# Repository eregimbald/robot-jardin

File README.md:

# robot-jardin

A controller to automate watering of an indoor tomato farm.

* Moisture sensors for soil.
* Solenoids to control watering.
* Hoses and T pieces to direct water into the pots.
* A LED light system. Mechanism to turn on and turn off the lights.
* Slack integration to the Raspberry Pi for control and monitoring.

## Requirements

### Platforms

- Raspbian

#### Configuration

##### wifi-interface
```
sudo nano /etc/network/interfaces

auto wlan0
iface wlan0 inet static
  address 192.168.1.180
  netmast 255.255.255.0
  gateway 192.168.1.1
  wpa-conf /etc/wpa_supplicant/wpa_supplicant.conf
```

##### wpa_supplicant
```
sudo nano /etc/wpa_supplicant/wpa_supplicant.conf

country=CA
ctrl_interface=DIR=/var/run/wpa_supplicant GROUP=netdev
update_config=1

network={
    ssid="ssid"
    psk="psk"
}
```

##### Enabling services
```
sudo raspi-config
Interfacing options
Enable ssh
Enable SPI
```
## Packages

Everything runs on Python3

### spidev
```
sudo apt-get install python3-spidev
wget https://github.com/Gadgetoid/py-spidev/archive/master.zip
unzip master.zip
rm master.zip
cd py-spidev-master
sudo python setup.py install
cd ..
```
### Adafruit Python GPIO
```
sudo apt-get update
sudo apt-get install build-essential python-pip python-dev python-smbus git
git clone https://github.com/adafruit/Adafruit_Python_GPIO.git
cd Adafruit_Python_GPIO
sudo python setup.py install
sudo python3 -m pip install git+git://github.com/chrisb2/pi_ina219.git
```
### Adafruit Python MCP3008
```
sudo apt-get update
sudo apt-get install build-essential python-dev python-smbus python-pip
sudo pip3 install adafruit-mcp3008
```
## MISC
https://github.com/stefanwichmann/kelvin

https://www.amazon.ca/Irrigation-System-Sprinkler-Watering-Outdoor/dp/B073NBHRRD/ref=sr_1_8?ie=UTF8&qid=1523198279&sr=8-8&keywords=plant+watering

http://www.davidhunt.ie/water-droplet-photography-with-raspberry-pi/

## Hardware
* To use a piece of proto board, with a Raspberry PI expansion connector.
* Thru-hole components
* A power adapter rated at 12V, 5A (this is more than enough, but commodity available on Amazon).
* A 5V regulator circuit (So we can use the same power brick for powering the PI as well).
* moisture sensors connected to an AD converter.
* water valve solenoid controlled by transistors.
* lights controlled by switching a plug.

Where possible datasheets for the parts we have thought about using are in the doc/datasheets folder.

## Raspberry Pi
We have the Raspberry Pi 3B. We want to use this, for the familiarity of programming language (Python).

Also we wish to have slack integration for remote query, monitoring, and control of the device.

### Power adapter
We needed 12V to drive the solenoid.  The solenoid takes about 100mA of power.  Plus we need to consider the power requirements of the Raspberry Pi.

We found this on Amazon for $12

It sais it is for LED strip lighting. 12V rated at 5A.  This will be more than enough for our uses.

## Voltage Regulator
Rather than needing a 2nd power brick adapter for powering the Raspberry Pi, which is another plug in the power bar, and another cable, and that micro USB power connector that never stays plugged in nicely (compared to a barrel jack power connector), it would be better if we could power the Raspberry Pi from our power adapter.

Several sites recommend that you use the USB input, because the Pi has built in power protection for you, so that if you accidentally give it more than 5V input you won't wreck you Pi.

Here, if we use a good 5V stable voltage regulator, then we should not have any problems with our Pi. Unless we drop the Pi into a bucket of water. But really that will have more problems than electrical power input considerations.

This was from a different project where I was going to use this to drive some stepper motors. It should have enough power to handle the Pi.

### Moisture Sensor Inputs
These moisture sensors came with a small intermediate circuit board. This module has a comparator on it, so that it can produce a digial output. Our initial experiments found this to be not very reliable or accurate, or consistent. Turning that little potentiometer is hard to get it to where we want. And also, what does it mean. It does not leave room for adjustments in software. The board also has an analog output. But really this is just using a resistor to create a voltage divider type of circuit across the probe input. We have chosen to use this analog mode of the sensor.  So instead of needing to use this little circuit board it would be better if we just built the components onto our own circuit board. This way we can have just a pair of wires from the circuit board to the moisture sensor.

We analyzed the circuit board and it contains these components.

Where the connector can be one of those screw terminal PCB mount connectors.  The wires we can use to go to the probe can be one of the pairs from a regular cat5 network cable type twisted pair wire, and then as long as we need to reach the potted plants from where the sensor is installed.

The sense goes straight into our analog to digital converter (currently the MCP3008 device).

When the soil is dry, the output will be a higher voltage. As the soil gets more moist, the probes will have a lower resistance, and thus create a lower voltage to the ADC.

Here we have chosen to use 3.3V as analog the input to the probes, since this is what the IO pins to the Raspberry Pi will use. The MCP3008 Supports separate Analog reference, but only as long as this is less than or equal to the VDD input.  Using 5V might possibly give us a better details when considering the small resistance that will be added from length of the wires to the probes. And 5V also lets us use faster samples. But really we are only going to be reading a few times a minute (or otherwise very low sample rate here).

#### One thing to note: Minimun dryness Threshold in software.

We should calibrate our software to expect the soil has a minimum dryness.  In that if the soil is below this threshold value then we do not attempt to try to water the soil. (e.g. we have a reading less than the maximum voltage possible).

This is because we have no way to differentiate between really dry soil, and if the probes are entirely not connected at all. such as there is no wires hooked up to the Raspberry Pi.  or in a more likely real world use case, if the wires on the probe corroded or the probe corroded or is no longer working.

In this situation (probes disconnected), when the soil appears dry to us, if we turn on the solenoid to let water in, the soil will never actually give a reading of "not dry" (because the probes are broken or disconnected). And we end up flooding the plants, and possibly making a mess of the apartment.

The proposal here then is to require the soil be some what moist. (e.g. so we are able to read a slightly lower voltage than just the max voltage). And then work with adjusting the soil moisture to be more moist within this. Assuming of course that we are able to read a minimum moisture that is within the range of what we would want the plants to be.

### Analog to digital controller
As discussed earlier, it is preferred we read the moisture sensor analog output, instead of its digital output, as our testing found there is not a very meaningful output from the moisture sensor digital output. Other than it is amusing for a test circuit on a breadboard.

The Raspberry Pi has no analog inputs. So we need something that can provide us with analog to digital conversion. For this we have selected the MCP3008 device.

This is because this is a popular and inexpensive device, that is available in a 16-dip package, and has a good community supported driver.

It also has 8 channels. So we can readily connect up to 8 analog inputs. Such as moisture sensors, or anything that can provide us a voltage , like ambient light sensors, noise sensors, pressure sensors, potentiometers, etc.

Our immediate use will be a few moisture sensors.

### Solenoid Driver
We can use a basic digital IO pin from the Raspberry Pi to drive a solenoid.  The solenoid we have choosen works around 12V and uses about 100mA of current. A simple transistor driver circuit is good enough for this.

But we thought there should be some short circuit protection, in case we short out the wires to the solenoid, or the solenoid becomes connected to ground. This circuit below attempts to provide this protection.

The input from the Raspberry Pi digital IO pin of logic level HIGH will turn on the solenoid.  I prefer this option from the usual Ali express type of relay board. Where they have the opto isolators and relays, which can be used for anything from 12 VDC to 120 VAC. But they are active low inputs. Which means when you power on the Pi and the GPIO pins are logic level LOW by default, this will turn on the relays until our software boots up and asserts logic level HIGH to the pin.

Practically these relay boards do this to allow for more general compatibility with microcontrollers. Most semiconductor devices are able to sink more current (pull a pin low) then they are able to source current (pull a pin high). Here this is a mute point since we are using a transitor driver which uses much less current than the opto isolators (about 20 mA) on a relay board.

The 12V power for the solenoid will be provided by the power supply brick above.

### Plug Driver
To control the lighting for the plants we assume something that can handle being powered on and off by unplugging it. Such as a lamp with a switch that can be turned on and have the lamp come on when it is plugged in.

We have thought about using relays, but really it is more elegant to use Triac device with an opto isolator. This is the same feature and behavior as a solid state relay, only not as expensive. Here we are assuming we ae not using heavily inductive loads and thus do not require power conditioning or snubbering (beyond what the Trac provides).

Using these STMicroelectronics Snubberless series Triacs.

We have a connector there for AC ground to be also our ground.

This is actually two swiches. The idea being that in a standard duplex plug there are two halves (top and bottom). So that we can provide individual switching to each half. Which will allow us to plug two lights into a single duplex plug.

The board can be laid out small enough to fit inside a metal duplex outlet style box. So that we can provide control wires into the box.
I was invisioning an extension cord with the metal plug box on the end with this controller board inside the metal box.

This keeps all of the 120V AC inside the extension cord and outlet box. We do not need to have 120V wires going out of the box to our circuit board. Which is a good thing here, since we are working with both water and electricity.

So to use this we will just need 2 digital IO pins from the Pi.

## IO expander

If we will have a lot of digital IO pins, such as to drive the solenoids and plug drivers, then it is recommended we look into a port expander.

A device such as the MPC32017 will do this well

here it requires (2) GPIO pins from the Raspberry Pi (the I2C bus pins) and provides us 16 pins, which can individually be configured as inputs or outputs.

If we were using them as digital inputs, then we would need some another GPIO pins for connecting those INTA, INTB pins. Which are for notifying the Raspberry Pi there is a pin state change on an input pin.

## Other Considerations

The site where this is installed should have a ground fault circuit interrupt (GFCI) type outlet installed into the wall.

This is where we will plug in
* The power adapter for powering the Raspberry Pi and solenoids and controlling the lights.
* The controlled plug for the lighting for the plants.

This is because we are working with water here.  According to Canadian buliding code, electrical applicances used near water, such as in a bathroom or kitchen, should be serviced from a GFCI outlet.

It is also beyond the scope of this project to instruct how to obtain and install a GFCI outlet. Consult your local electrician or home improvement store.

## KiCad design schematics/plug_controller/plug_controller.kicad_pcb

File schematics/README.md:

# Schematics
These are KiCAD projects.

KiCAD is an  cross platform and open source Electronics Design Automation Suite.

We used it here for making schematic diagrams and where we had a PCB made, the PCB layout.

You can get it here: [KiCAD Project](http://kicad-pcb.org/)

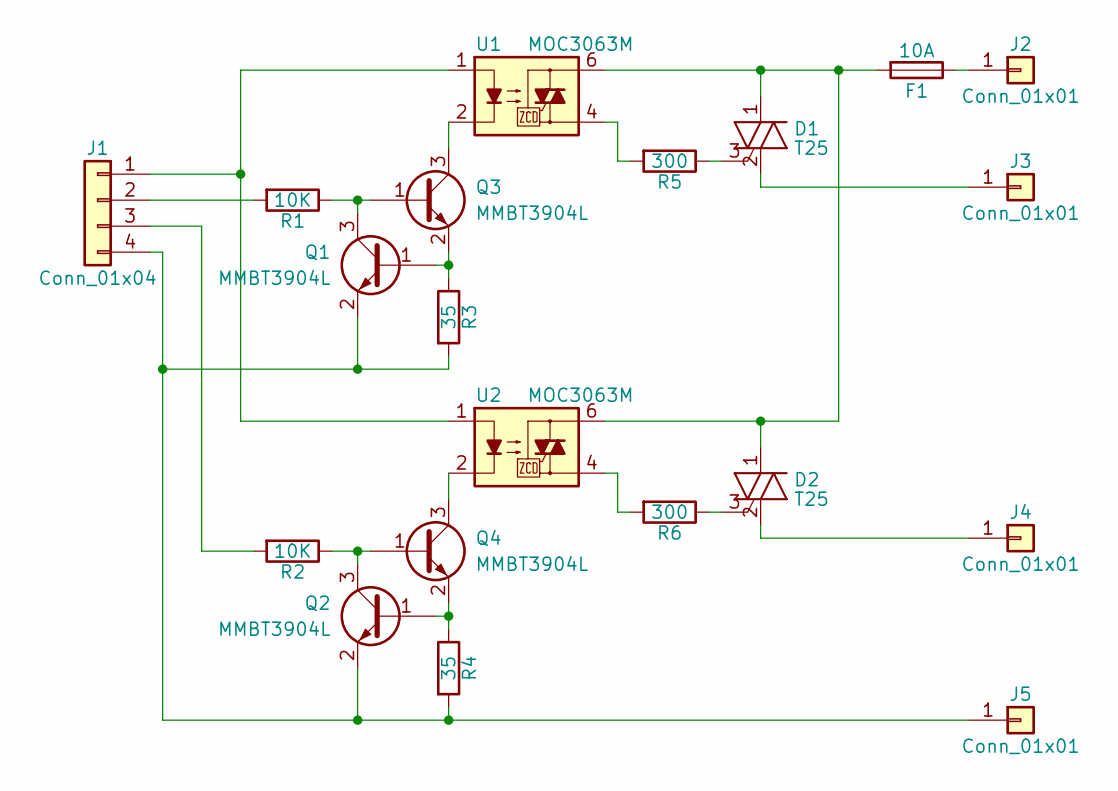
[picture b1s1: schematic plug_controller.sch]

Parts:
D1, D2: T25; D2PAK
F1: 10A; Fuseholder5x20_horiz_open_inline_Type-I
J1: Conn_01x04; Molex_KK-6410-04_04x2.54mm_Straight
J2, J3, J4, J5: Conn_01x01; TAB_0.250_SOLDER
Q1, Q2, Q3, Q4: MMBT3904L; SOT-23
R1, R2: 10K; R_0603
R3, R4: 35; R_0603
R5, R6: 300; R_0603
U1, U2: MOC3063M; 6-SMD_Gullwing

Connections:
unnamed: D1.1 (A1), D2.1 (A1), F1.2, U1.6, U2.6
unnamed: D1.2 (A2), J3.1
unnamed: D1.3 (G), R5.1
unnamed: D2.2 (A2), J4.1
unnamed: D2.3 (G), R6.1
unnamed: F1.1, J2.1
unnamed: J1.1, U1.1, U2.1
unnamed: J1.2, R1.2
unnamed: J1.3, R2.2
unnamed: J1.4, J5.1, Q1.2 (E), Q2.2 (E), R3.2, R4.2
unnamed: Q1.1 (B), Q3.2 (E), R3.1
unnamed: Q1.3 (C), Q3.1 (B), R1.1
unnamed: Q2.1 (B), Q4.2 (E), R4.1
unnamed: Q2.3 (C), Q4.1 (B), R2.1
unnamed: Q3.3 (C), U1.2
unnamed: Q4.3 (C), U2.2
unnamed: R5.2, U1.4
unnamed: R6.2, U2.4

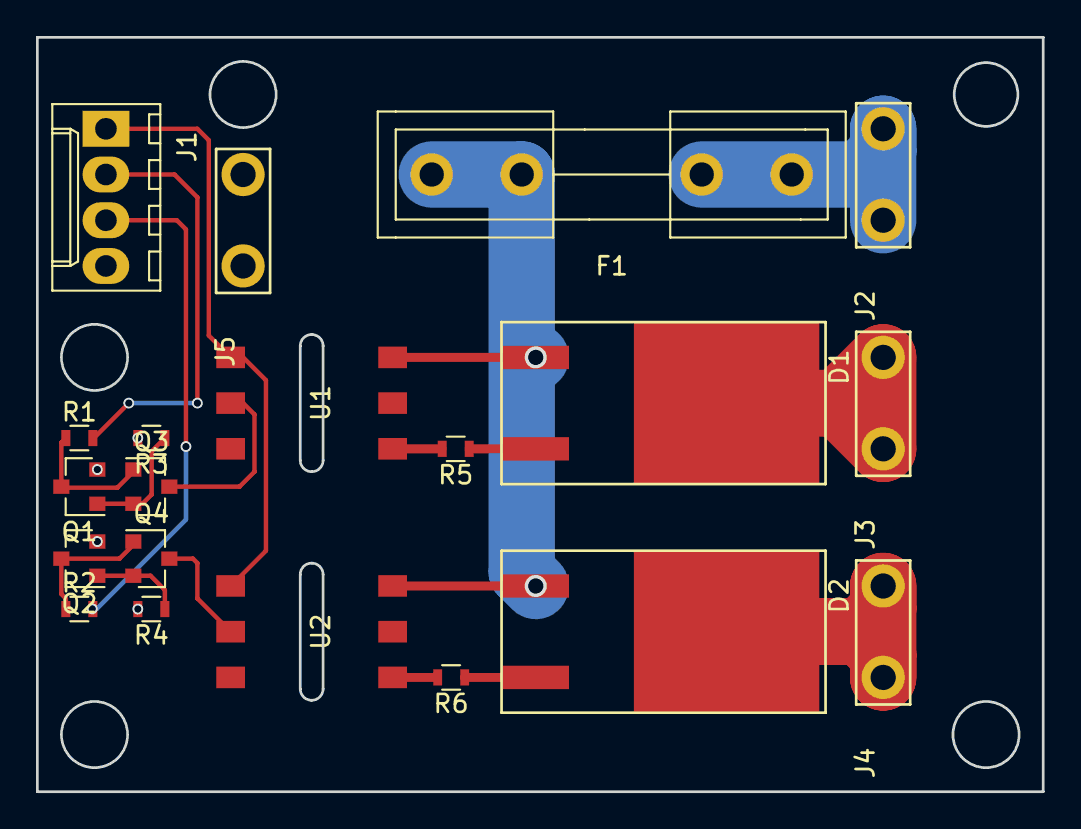
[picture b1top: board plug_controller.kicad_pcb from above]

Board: 2 copper layers, 55.9 x 41.9 mm, 20 parts (0 on the bottom side), 18 nets.

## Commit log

2018-04-13 readme updates
2018-04-13 Readme update
2018-04-14 create a concept picture
2018-04-15 do some design documentation.
    some schematics
    finding datasheets for the components we were thinking about using
    pictures of the schematics in the README.
2018-04-15 small edits after proof reading
2018-04-29 update footprints as assembling first design.
    The triac pins were reversed.
    The fuse footprints were not the holders i have.
    The resistor between optotriac and triac should be larger.
